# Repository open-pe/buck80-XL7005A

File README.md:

* non-synchronous buck converter at 150 KHz
* 5 - 80V input
* 1.25 - 20V output
* 0.4A output current
* 1V min voltage drop

* [XL7005A](https://www.lcsc.com/datasheet/lcsc_datasheet_1811081614_XLSEMI-XL7005A_C50848.pdf) controller IC
* RC-Snubber

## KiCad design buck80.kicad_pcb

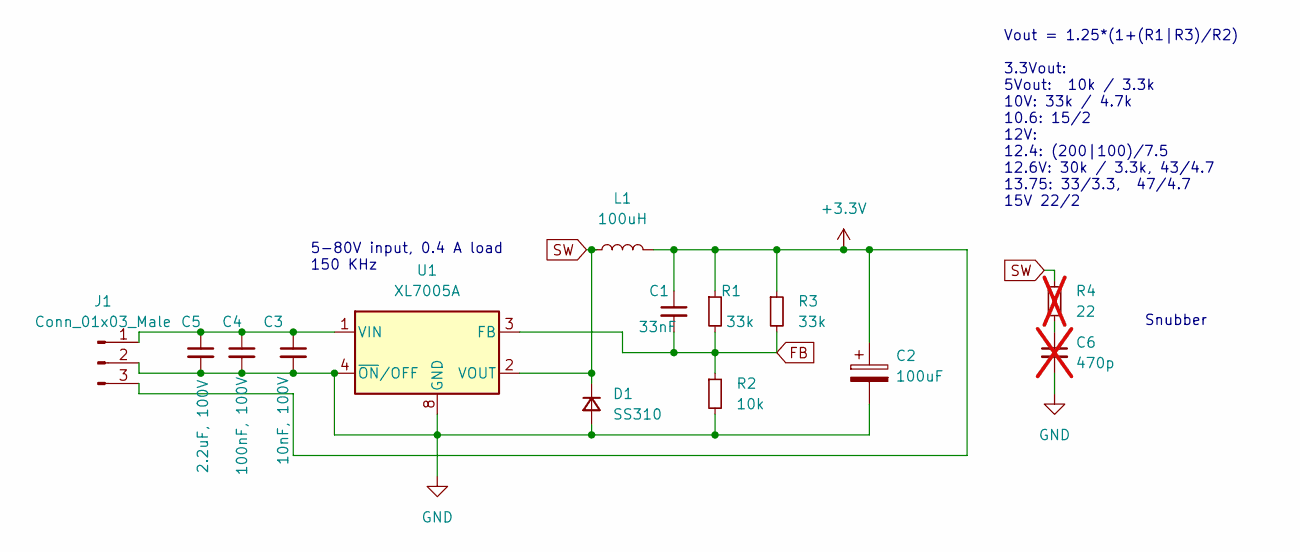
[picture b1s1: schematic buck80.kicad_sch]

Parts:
C1: 33nF; C_0805_2012Metric
C2: 100uF; CP_Elec_6.3x5.9
C3: 10nF, 100V; C_0805_2012Metric
C4: 100nF, 100V; C_1206_3216Metric
C5: 2.2uF, 100V; C_1206_3216Metric
C6: 470p; C_0603_1608Metric; not fitted
D1: SS310; D_SMA_Handsoldering
J1: Conn_01x03_Male; PinHeader_1x03_P2.54mm_Vertical
L1: 100uH; L_Taiyo-Yuden_NR-50xx_HandSoldering
R1, R3: 33k; R_0805_2012Metric
R2: 10k; R_0805_2012Metric
R4: 22; R_0603_1608Metric; not fitted
U1: XL7005A; SOIC-8_3.9x4.9mm_P1.27mm

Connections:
+3.3V: C1.1, C2.1, J1.3, L1.2, R1.1, R3.1
FB: C1.2, R1.2, R2.1, R3.2, U1.3 (FB)
GND: C2.2, C3.2, C4.2, C5.2, C6.2, D1.2 (A), J1.2, R2.2, U1.4 (~ON/OFF), U1.5 (GND), U1.6 (GND), U1.7 (GND), U1.8 (GND)
unnamed: C6.1, R4.2
unnamed: C3.1, C4.1, C5.1, J1.1, U1.1 (VIN)
SW: D1.1 (K), L1.1, R4.1, U1.2 (VOUT)

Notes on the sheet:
Snubber
5-80V input, 0.4 A load 150 KHz
Vout = 1.25*(1+(R1|R3)/R2) 3.3Vout: 5Vout: 10k / 3.3k 10V: 33k / 4.7k 10.6: 15/2 12V: 12.4: (200|100)/7.5 12.6V: 30k / 3.3k, 43/4.7 13.75: 33/3.3, 47/4.7 15V 22/2

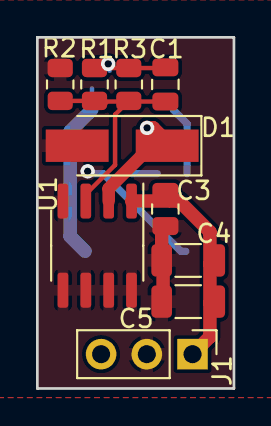
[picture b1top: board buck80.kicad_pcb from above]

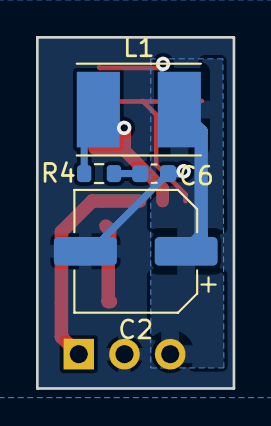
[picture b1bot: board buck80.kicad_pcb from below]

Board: 2 copper layers, 10.9 x 19.5 mm, 14 parts (4 on the bottom side), 6 nets.

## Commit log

2024-10-25 add files
